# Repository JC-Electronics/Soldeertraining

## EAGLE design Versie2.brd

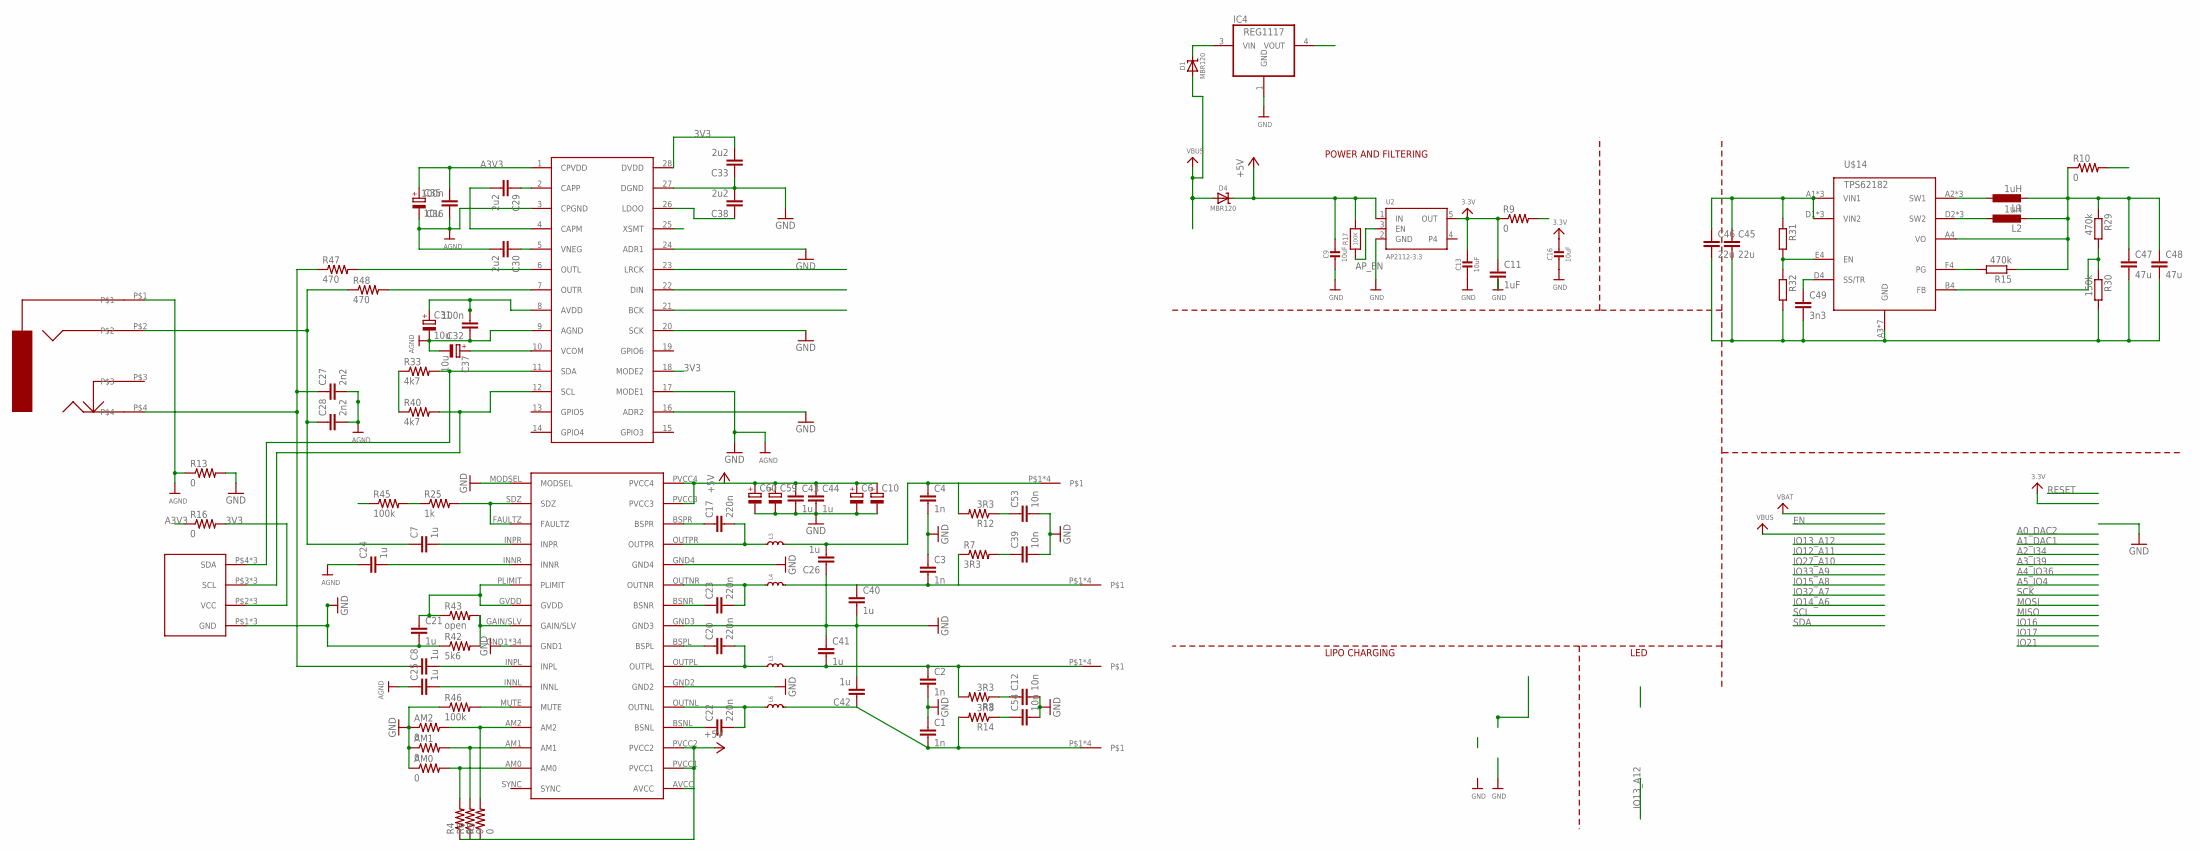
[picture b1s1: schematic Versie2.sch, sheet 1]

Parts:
AM0, AM1, AM2: 0; R0402
C1, C2, C3, C4: 1n; C0805
C6, C10, C59, C60: CPOL-EUE5-13; E5-13
C7, C8, C24, C25, C26, C40, C41, C42, C43, C44: 1u; C1206
C9, C13, C16: 10uF; 0805-NO
C11: 1uF; C1206
C12, C39, C53, C54: 10n; C0805
C17, C20, C22, C23: 220n; C0805K
C21: 1u; C0805K
C27, C28: 2n2; C0805K
C29, C30, C33, C38: 2u2; C1206K
C31, C35, C37: 10u; UD-4X5,8_NICHICON
C32, C36: 100n; C0603K
C45, C46: 22u; C0805K
C47, C48: 47u; C0805K
C49: 3n3; C0603
D1, D4: MBR120; SOD-123
IC4: REG1117; SOT223
L1, L2: 1uH; L4532P
L3, L4, L5, L6: INDUCTOR-SRN6045; SRN6045
R4, R5, R6: 0; R0402
R7, R8, R12, R14: 3R3; R0805
R9, R10, R13, R16: 0; R0805
R15, R29: 470k; R0402
R17: 100K; 0603-NO
R25: 1k; R0402
R30: 150k; R0402
R31, R32: R-EU_R0402; R0402
R33, R40: 4k7; R0805
R42: 5k6; R0402
R43: open; R0402
R45, R46: 100k; R0402
R47, R48: 470; R0805
U1: PCM5122; TSSOP-28
U2: AP2112-3.3; SOT23-5
U4: TPA3130; TSSOP32-GROUNDPAD
U$2: DISPLAY
U$9, U$16, U$22, U$23: SCREWCON
U$14: TPS62182; DSBGA24
U$26: JACKSTRAIGHTUP

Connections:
3.3V: C11.1, C13.1, C16.1, R9.1, U2.5 (OUT); also elsewhere on the board
3V3: C33.2, R9.2, R10.2, R16.2, R33.1, R40.1, U1.18 (MODE2), U1.25 (XSMT), U1.28 (DVDD), U$2.P$2 (VCC), U$2.P$10 (VCC), U$2.P$14 (VCC); also elsewhere on the board
+5V: C9.1, C45.1, C46.1, D4.C, IC4.4 (VOUT), R17.2, R31.1, U2.1 (IN), U$14.A1 (VIN1), U$14.B1 (VIN1), U$14.C1 (VIN1), U$14.D1 (VIN2), U$14.E1 (VIN2), U$14.F1 (VIN2)
A3V3: C31.+, C32.2, C35.+, C36.2, R16.1, U1.1 (CPVDD), U1.8 (AVDD)
AGND: C24.1, C25.1, C27.2, C28.2, C30.2, C31.-, C32.1, C35.-, C36.1, C37.-, R13.1, U1.3 (CPGND), U1.9 (AGND), U$26.P$1
AP_EN: R17.1, U2.3 (EN)
GND: AM0.1, AM1.1, AM2.1, C1.1, C2.2, C3.1, C4.2, C6.-, C9.2, C10.-, C11.2, C12.2, C13.2, C16.2, C21.2, C26.1, C33.1, C38.2, C39.2, C40.2, C41.1, C42.2, C43.2, C44.2, C45.2, C46.2, C47.2, C48.2, C49.2, C53.2, C54.2, C59.-, C60.-, IC4.1 (GND), R13.2, R30.2, R32.2, R42.1, R45.1, R46.1, U1.16 (ADR2), U1.17 (MODE1), U1.20 (SCK), U1.24 (ADR1), U1.27 (DGND), U2.2 (GND), U4.GND1, U4.GND2, U4.GND3, U4.GND4, U4.MODSEL, U4.P$33 (GND1), U4.P$34 (GND1), U4.P$35 (GND1), U4.P$36 (GND1), U4.P$37 (GND1), U4.P$38 (GND1), U4.P$39 (GND1), U4.P$40 (GND1), U4.P$41 (GND1), U4.P$42 (GND1), U4.P$43 (GND1), U4.P$44 (GND1), U4.P$45 (GND1), U4.P$46 (GND1), U4.P$47 (GND1), U4.P$48 (GND1), U4.P$49 (GND1), U4.P$50 (GND1), U4.P$51 (GND1), U4.P$52 (GND1), U4.P$53 (GND1), U4.P$54 (GND1), U4.P$55 (GND1), U4.P$56 (GND1), U4.P$57 (GND1), U4.P$58 (GND1), U4.P$59 (GND1), U4.P$60 (GND1), U4.P$61 (GND1), U4.P$62 (GND1), U4.P$63 (GND1), U4.P$64 (GND1), U4.POWERPAD (GND1), U$2.P$1 (GND), U$2.P$9 (GND), U$2.P$13 (GND), U$14.A3 (GND), U$14.B3 (GND), U$14.C3 (GND), U$14.C4 (GND), U$14.D3 (GND), U$14.E3 (GND), U$14.F3 (GND); also elsewhere on the board
IO18: R25.1, R45.2; also elsewhere on the board
IO25: U1.23 (LRCK); also elsewhere on the board
IO26: U1.22 (DIN); also elsewhere on the board
IO27: U1.21 (BCK); also elsewhere on the board
IO32: R40.2, U1.12 (SCL), U$2.P$3 (SCL), U$2.P$11 (SCL), U$2.P$15 (SCL); also elsewhere on the board
IO33: R33.2, U1.11 (SDA), U$2.P$4 (SDA), U$2.P$12 (SDA), U$2.P$16 (SDA); also elsewhere on the board
LEFT+: C2.1, C41.2, L5.2, R8.2, U$22.P$1, U$22.P$2, U$22.P$3, U$22.P$4
LEFT-: C1.2, C42.1, L6.2, R14.2, U$23.P$1, U$23.P$2, U$23.P$3, U$23.P$4
unnamed: C54.1, R14.1
unnamed: C53.1, R12.1
unnamed: C12.1, R8.1
unnamed: C8.1, C27.1, R47.1, U$26.P$4
unnamed: C7.1, C28.1, R48.1, U$26.P$2
unnamed: C39.1, R7.2
unnamed: C7.2, U4.INPR
unnamed: C8.2, U4.INPL
unnamed: R48.2, U1.7 (OUTR)
unnamed: R25.2, U4.FAULTZ, U4.SDZ
unnamed: C49.1, U$14.D4 (SS/TR)
unnamed: L1.1, U$14.A2 (SW1), U$14.B2 (SW1), U$14.C2 (SW1)
unnamed: L2.1, U$14.D2 (SW2), U$14.E2 (SW2), U$14.F2 (SW2)
unnamed: R15.2, U$14.F4 (PG)
unnamed: R29.2, R30.1, U$14.B4 (FB)
unnamed: R31.2, R32.1, U$14.E4 (EN)
unnamed: C24.2, U4.INNR
unnamed: C25.2, U4.INNL
unnamed: C21.1, R43.1, U4.GVDD, U4.PLIMIT
unnamed: C17.1, U4.BSPR
unnamed: C17.2, L3.1, U4.OUTPR
unnamed: C20.1, U4.BSPL
unnamed: C20.2, L5.1, U4.OUTPL
unnamed: C23.2, L4.1, U4.OUTNR
unnamed: C23.1, U4.BSNR
unnamed: C22.1, U4.BSNL
unnamed: C22.2, L6.1, U4.OUTNL
unnamed: R42.2, R43.2, U4.GAIN/SLV
unnamed: R46.2, U4.MUTE
unnamed: R47.2, U1.6 (OUTL)
unnamed: C29.2, U1.4 (CAPM)
unnamed: C29.1, U1.2 (CAPP)
unnamed: C30.1, U1.5 (VNEG)
unnamed: C37.+, U1.10 (VCOM)
unnamed: C38.1, U1.26 (LDOO)
unnamed: AM0.2, R4.2, U4.AM0
unnamed: AM1.2, R6.2, U4.AM1
unnamed: AM2.2, R5.2, U4.AM2
OUTDCDC: C47.1, C48.1, L1.2, L2.2, R10.1, R15.1, R29.1, U$14.A4 (VO); also elsewhere on the board
RIGHT+: C4.1, C26.2, L3.2, R12.2, U$9.P$1, U$9.P$2, U$9.P$3, U$9.P$4
RIGHT-: C3.2, C40.1, L4.2, R7.1, U$16.P$1, U$16.P$2, U$16.P$3, U$16.P$4
VBUS: D1.A, D4.A; also elsewhere on the board
VCC: C6.+, C10.+, C43.1, C44.1, C59.+, C60.+, D1.C, IC4.3 (VIN), R4.1, R5.1, R6.1, U4.AVCC, U4.PVCC1, U4.PVCC2, U4.PVCC3, U4.PVCC4; also elsewhere on the board

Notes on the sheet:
POWER AND FILTERING
LIPO CHARGING
LED

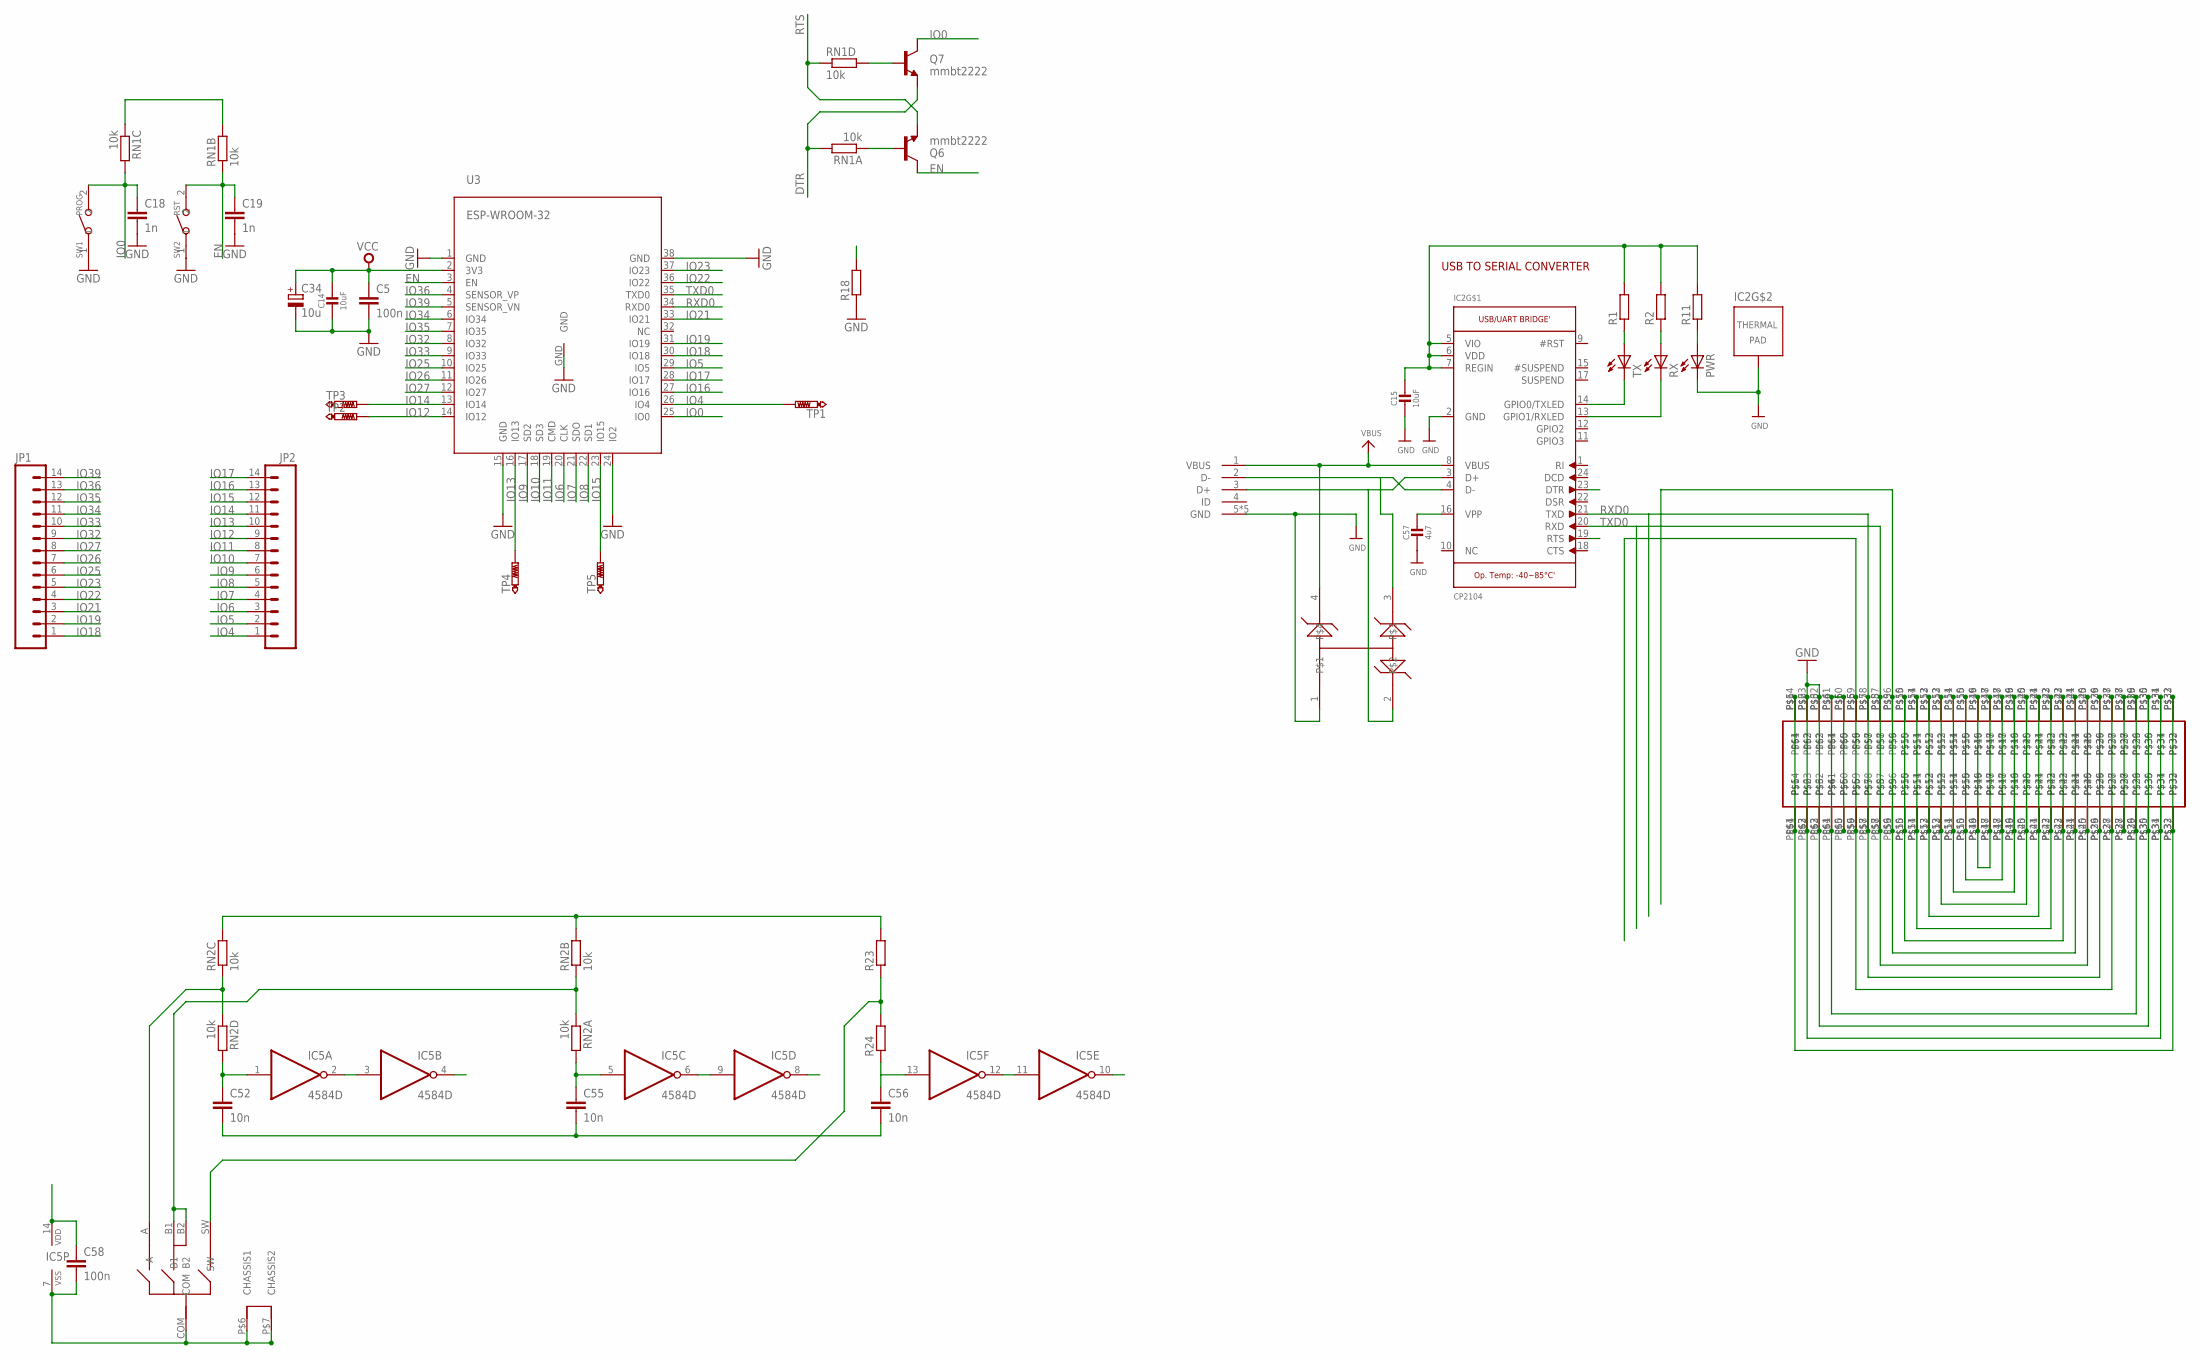
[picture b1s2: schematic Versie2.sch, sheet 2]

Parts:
C5, C58: 100n; C0603
C14, C15: 10uF; 0805-NO
C18, C19: 1n; C0805
C34: 10u; UD-4X5,8_NICHICON
C52, C55, C56: 10n; C0805
C57: 4u7; 0805-NO
D5: SP0503; SOT143
IC2: CP2104; QFN24_4MM_SMSC
IC5: 4584D; SO14
JP1, JP2: M14; 1X14
PWR: LEDCHIPLED_0603; CHIPLED_0603
Q6, Q7: mmbt2222; SOT23-3
R1, R2, R11: R-EU_R0402; R0402
R18: R-EU_R0805; R0805
R23, R24: R-EU_R0603; R0603
RN1, RN2: 10k; RN8P-4R-CRA06S
RX: LEDCHIPLED_0603; CHIPLED_0603
SW1: PROG; SW2-4.0-6.0X3.0X2.5MM
SW2: RST; SW2-4.0-6.0X3.0X2.5MM
TP1, TP2, TP3, TP4, TP5: PTR1B1,27; B1,27
TX: LEDCHIPLED_0603; CHIPLED_0603
U3: ESP-WROOM-32
U$1, U$13: 0714360864
U$41: ROTARY; ENCODER
USB: JRUSB; MICRO-B-SMT

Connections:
3.3V: U$1.P$15, U$1.P$18, U$1.P$47, U$1.P$50, U$13.P$15, U$13.P$18, U$13.P$47, U$13.P$50; also elsewhere on the board
3V3: C5.1, C14.1, C15.1, C34.+, C58.1, IC2.5 (VIO), IC2.6 (VDD), IC2.7 (REGIN), IC5.14 (VDD), R1.2, R2.2, R11.2, R23.2, RN1.3 (1), RN1.7 (2), RN2.6 (2), RN2.7 (2), U3.2 (3V3), U$1.P$16, U$1.P$17, U$1.P$48, U$1.P$49, U$13.P$16, U$13.P$17, U$13.P$48, U$13.P$49; also elsewhere on the board
DTR: IC2.23 (DTR), Q7.2 (E), RN1.8 (2)
EN: C19.1, Q6.3 (C), RN1.2 (1), SW2.2, U3.3 (EN), U$1.P$6, U$1.P$27, U$1.P$38, U$1.P$59, U$13.P$6, U$13.P$27, U$13.P$38, U$13.P$59
GND: C5.2, C14.2, C15.2, C18.2, C19.2, C34.-, C52.2, C55.2, C56.2, C57.2, C58.2, D5.1, IC2.2 (GND), IC2.THERM (TP), IC5.7 (VSS), PWR.C, R18.1, SW1.1, SW2.1, U3.1 (GND), U3.15 (GND), U3.24 (IO2), U3.38 (GND), U3.GND, U$1.P$2, U$1.P$3, U$1.P$30, U$1.P$31, U$1.P$34, U$1.P$35, U$1.P$62, U$1.P$63, U$13.P$2, U$13.P$3, U$13.P$30, U$13.P$31, U$13.P$34, U$13.P$35, U$13.P$62, U$13.P$63, U$41.COM, U$41.P$6 (CHASSIS1), U$41.P$7 (CHASSIS2), USB.5 (GND), USB.P$6 (GND), USB.P$7 (GND), USB.P$8 (GND), USB.P$9 (GND); also elsewhere on the board
GND1: R18.2
IO0: C18.1, Q7.3 (C), RN1.6 (2), SW1.2, U3.25 (IO0), U$1.P$9, U$1.P$24, U$1.P$41, U$1.P$56, U$13.P$9, U$13.P$24, U$13.P$41, U$13.P$56
IO4: JP2.1, TP1.TP, U3.26 (IO4)
IO5: IC5.10 (O), JP2.2, U3.29 (IO5)
IO6: JP2.3, U3.20 (CLK)
IO7: JP2.4, U3.21 (SDO)
IO8: JP2.5, U3.22 (SD1)
IO9: JP2.6, U3.17 (SD2)
IO10: JP2.7, U3.18 (SD3)
IO11: JP2.8, U3.19 (CMD)
IO12: JP2.9, TP2.TP, U3.14 (IO12)
IO13: JP2.10, TP4.TP, U3.16 (IO13)
IO14: JP2.11, TP3.TP, U3.13 (IO14)
IO15: JP2.12, TP5.TP, U3.23 (IO15)
IO16: IC5.8 (O), JP2.13, U3.27 (IO16)
IO17: IC5.4 (O), JP2.14, U3.28 (IO17)
IO18: JP1.1, U3.30 (IO18); also elsewhere on the board
IO19: JP1.2, U3.31 (IO19)
IO21: JP1.3, U3.33 (IO21)
IO22: JP1.4, U3.36 (IO22)
IO23: JP1.5, U3.37 (IO23)
IO25: JP1.6, U3.10 (IO25); also elsewhere on the board
IO26: JP1.7, U3.11 (IO26); also elsewhere on the board
IO27: JP1.8, U3.12 (IO27); also elsewhere on the board
IO32: JP1.9, U3.8 (IO32); also elsewhere on the board
IO33: JP1.10, U3.9 (IO33); also elsewhere on the board
IO34: JP1.11, U3.6 (IO34)
IO35: JP1.12, U3.7 (IO35)
IO36: JP1.13, U3.4 (SENSOR_VP)
IO39: JP1.14, U3.5 (SENSOR_VN)
unnamed: RN2.3 (1), RN2.4 (1), U$41.A
unnamed: D5.3, IC2.4 (D-), USB.2 (D-)
unnamed: IC5.11 (I), IC5.12 (O)
unnamed: RN2.1, RN2.2 (1), U$41.B1, U$41.B2
unnamed: C52.1, IC5.1 (I), RN2.5 (2)
unnamed: D5.2, IC2.3 (D+), USB.3 (D+)
unnamed: C55.1, IC5.5 (I), RN2.8 (2)
unnamed: R23.1, R24.2, U$41.SW
unnamed: Q7.1 (B), RN1.5 (2)
unnamed: C57.1, IC2.16 (VPP)
unnamed: Q6.1 (B), RN1.1
unnamed: PWR.A, R11.1
unnamed: IC2.14 (GPIO0/TXLED), TX.C
unnamed: IC2.13 (GPIO1/RXLED), RX.C
unnamed: R1.1, TX.A
unnamed: U$1.P$10, U$1.P$23, U$1.P$42, U$1.P$55, U$13.P$10, U$13.P$23, U$13.P$42, U$13.P$55
unnamed: U$1.P$11, U$1.P$22, U$1.P$43, U$1.P$54, U$13.P$11, U$13.P$22, U$13.P$43, U$13.P$54
unnamed: U$1.P$12, U$1.P$21, U$1.P$44, U$1.P$53, U$13.P$12, U$13.P$21, U$13.P$44, U$13.P$53
unnamed: U$1.P$13, U$1.P$20, U$1.P$45, U$1.P$52, U$13.P$13, U$13.P$20, U$13.P$45, U$13.P$52
unnamed: R2.1, RX.A
unnamed: IC5.2 (O), IC5.3 (I)
unnamed: IC5.6 (O), IC5.9 (I)
unnamed: C56.1, IC5.13 (I), R24.1
OUTDCDC: U$1.P$14, U$1.P$19, U$1.P$46, U$1.P$51, U$13.P$14, U$13.P$19, U$13.P$46, U$13.P$51; also elsewhere on the board
RTS: IC2.19 (RTS), Q6.2 (E), RN1.4 (1)
RXD0: IC2.21 (TXD), U3.34 (RXD0), U$1.P$7, U$1.P$26, U$1.P$39, U$1.P$58, U$13.P$7, U$13.P$26, U$13.P$39, U$13.P$58
TXD0: IC2.20 (RXD), U3.35 (TXD0), U$1.P$8, U$1.P$25, U$1.P$40, U$1.P$57, U$13.P$8, U$13.P$25, U$13.P$40, U$13.P$57
VBUS: D5.4, IC2.8 (VBUS), U$1.P$1, U$1.P$32, U$1.P$33, U$1.P$64, U$13.P$1, U$13.P$32, U$13.P$33, U$13.P$64, USB.1 (VBUS); also elsewhere on the board
VCC: U$1.P$4, U$1.P$5, U$1.P$28, U$1.P$29, U$1.P$36, U$1.P$37, U$1.P$60, U$1.P$61, U$13.P$4, U$13.P$5, U$13.P$28, U$13.P$29, U$13.P$36, U$13.P$37, U$13.P$60, U$13.P$61; also elsewhere on the board

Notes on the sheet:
USB TO SERIAL CONVERTER

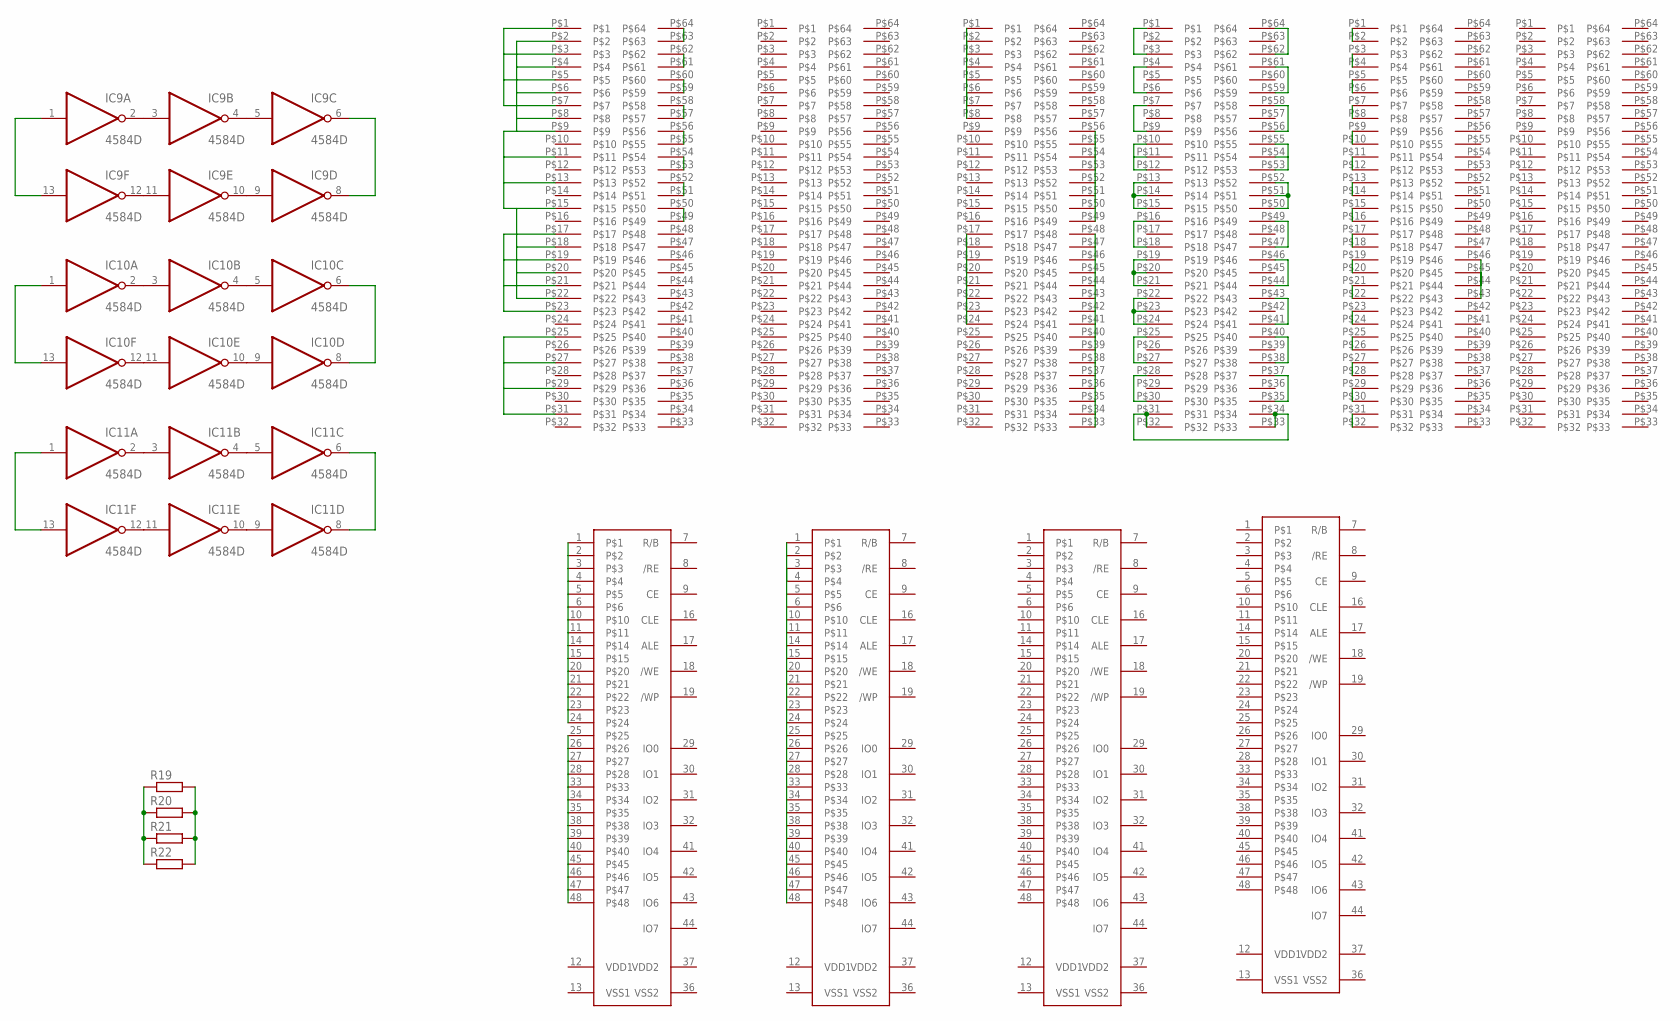
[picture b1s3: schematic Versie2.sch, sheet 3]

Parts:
IC9, IC10, IC11: 4584D; SO14
IC12, IC13, IC14, IC15: K9F5608; TSOP48
R19, R20, R21, R22: R-EU_0207/15; 0207/15
U$5, U$21, U$24, U$32, U$42, U$43: BGA64

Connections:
unnamed: IC9.2 (O), IC9.3 (I)
unnamed: IC9.4 (O), IC9.5 (I)
unnamed: IC9.9 (I), IC9.10 (O)
unnamed: IC9.6 (O), IC9.8 (O)
unnamed: IC9.1 (I), IC9.13 (I)
unnamed: IC9.11 (I), IC9.12 (O)
unnamed: IC10.2 (O), IC10.3 (I)
unnamed: IC10.4 (O), IC10.5 (I)
unnamed: IC10.9 (I), IC10.10 (O)
unnamed: IC10.6 (O), IC10.8 (O)
unnamed: IC10.1 (I), IC10.13 (I)
unnamed: IC10.11 (I), IC10.12 (O)
unnamed: IC11.2 (O), IC11.3 (I)
unnamed: IC11.4 (O), IC11.5 (I)
unnamed: IC11.9 (I), IC11.10 (O)
unnamed: IC11.6 (O), IC11.8 (O)
unnamed: IC11.1 (I), IC11.13 (I)
unnamed: IC11.11 (I), IC11.12 (O)
unnamed: R19.1, R20.1, R21.1, R22.1
unnamed: R19.2, R20.2, R21.2, R22.2
unnamed: U$5.P$17, U$5.P$19, U$5.P$21, U$5.P$23
unnamed: IC13.1, IC13.2, IC13.3, IC13.4, IC13.5, IC13.6, IC13.10, IC13.11, IC13.14, IC13.15, IC13.20, IC13.21, IC13.22, IC13.23, IC13.24
unnamed: U$42.P$27, U$42.P$28
unnamed: U$42.P$29, U$42.P$30
unnamed: U$42.P$25, U$42.P$26
unnamed: U$42.P$23, U$42.P$24
unnamed: U$42.P$21, U$42.P$22
unnamed: U$42.P$19, U$42.P$20
unnamed: U$42.P$17, U$42.P$18
unnamed: U$42.P$15, U$42.P$16
unnamed: U$42.P$13, U$42.P$14
unnamed: U$42.P$11, U$42.P$12
unnamed: U$42.P$9, U$42.P$10
unnamed: U$42.P$7, U$42.P$8
unnamed: U$42.P$5, U$42.P$6
unnamed: U$42.P$3, U$42.P$4
unnamed: U$42.P$1, U$42.P$2
unnamed: U$42.P$31, U$42.P$32
unnamed: U$32.P$62, U$32.P$64
unnamed: U$32.P$59, U$32.P$61
unnamed: U$32.P$56, U$32.P$58
unnamed: U$32.P$53, U$32.P$54, U$32.P$55
unnamed: U$32.P$50, U$32.P$51, U$32.P$52
unnamed: U$32.P$47, U$32.P$49
unnamed: U$32.P$44, U$32.P$46
unnamed: U$32.P$41, U$32.P$43
unnamed: U$32.P$38, U$32.P$40
unnamed: U$32.P$35, U$32.P$37
unnamed: U$5.P$1, U$5.P$3, U$5.P$5, U$5.P$7
unnamed: U$5.P$63, U$5.P$64
unnamed: U$5.P$25, U$5.P$27, U$5.P$29, U$5.P$31
unnamed: U$5.P$2, U$5.P$4, U$5.P$6, U$5.P$8, U$5.P$9, U$5.P$11, U$5.P$13, U$5.P$15, U$5.P$18, U$5.P$20, U$5.P$22
unnamed: U$5.P$61, U$5.P$62
unnamed: U$5.P$59, U$5.P$60
unnamed: U$5.P$57, U$5.P$58
unnamed: U$5.P$55, U$5.P$56
unnamed: U$5.P$53, U$5.P$54
unnamed: U$5.P$51, U$5.P$52
unnamed: U$5.P$49, U$5.P$50
unnamed: U$42.P$43, U$42.P$44, U$42.P$45, U$42.P$46
unnamed: U$32.P$1, U$32.P$3
unnamed: U$32.P$4, U$32.P$6
unnamed: U$32.P$7, U$32.P$9
unnamed: U$32.P$10, U$32.P$11, U$32.P$12
unnamed: U$32.P$13, U$32.P$14, U$32.P$15
unnamed: U$32.P$16, U$32.P$18
unnamed: U$32.P$19, U$32.P$20, U$32.P$21
unnamed: U$32.P$22, U$32.P$23, U$32.P$24
unnamed: U$32.P$25, U$32.P$27
unnamed: U$32.P$28, U$32.P$30
unnamed: U$32.P$31, U$32.P$32, U$32.P$33, U$32.P$34
unnamed: U$24.P$1, U$24.P$2, U$24.P$3, U$24.P$4, U$24.P$5, U$24.P$6, U$24.P$7, U$24.P$8
unnamed: U$24.P$17, U$24.P$18, U$24.P$19, U$24.P$20, U$24.P$21, U$24.P$22, U$24.P$23, U$24.P$24
unnamed: U$24.P$49, U$24.P$50, U$24.P$51, U$24.P$52, U$24.P$53, U$24.P$54, U$24.P$55, U$24.P$56
unnamed: U$24.P$33, U$24.P$34, U$24.P$35, U$24.P$36, U$24.P$37, U$24.P$38, U$24.P$39, U$24.P$40, U$24.P$41, U$24.P$42, U$24.P$43, U$24.P$44, U$24.P$45, U$24.P$46, U$24.P$47, U$24.P$48
unnamed: IC13.25, IC13.26, IC13.27, IC13.28, IC13.33, IC13.34, IC13.35, IC13.38, IC13.39, IC13.40, IC13.45, IC13.46, IC13.47, IC13.48
unnamed: IC14.1, IC14.2, IC14.3, IC14.4, IC14.5, IC14.6, IC14.10, IC14.11, IC14.14, IC14.15, IC14.20, IC14.21, IC14.22, IC14.23, IC14.24, IC14.25, IC14.26, IC14.27, IC14.28, IC14.33, IC14.34, IC14.35, IC14.38, IC14.39, IC14.40, IC14.45, IC14.46, IC14.47, IC14.48
VDD: IC9.14 (VDD), IC10.14 (VDD), IC11.14 (VDD)
VDD1: IC12.12 (VDD1), IC13.12 (VDD1), IC14.12 (VDD1), IC15.12 (VDD1)
VDD2: IC12.37 (VDD2), IC13.37 (VDD2), IC14.37 (VDD2), IC15.37 (VDD2)
VSS: IC9.7 (VSS), IC10.7 (VSS), IC11.7 (VSS)
VSS1: IC12.13 (VSS1), IC13.13 (VSS1), IC14.13 (VSS1), IC15.13 (VSS1)
VSS2: IC12.36 (VSS2), IC13.36 (VSS2), IC14.36 (VSS2), IC15.36 (VSS2)

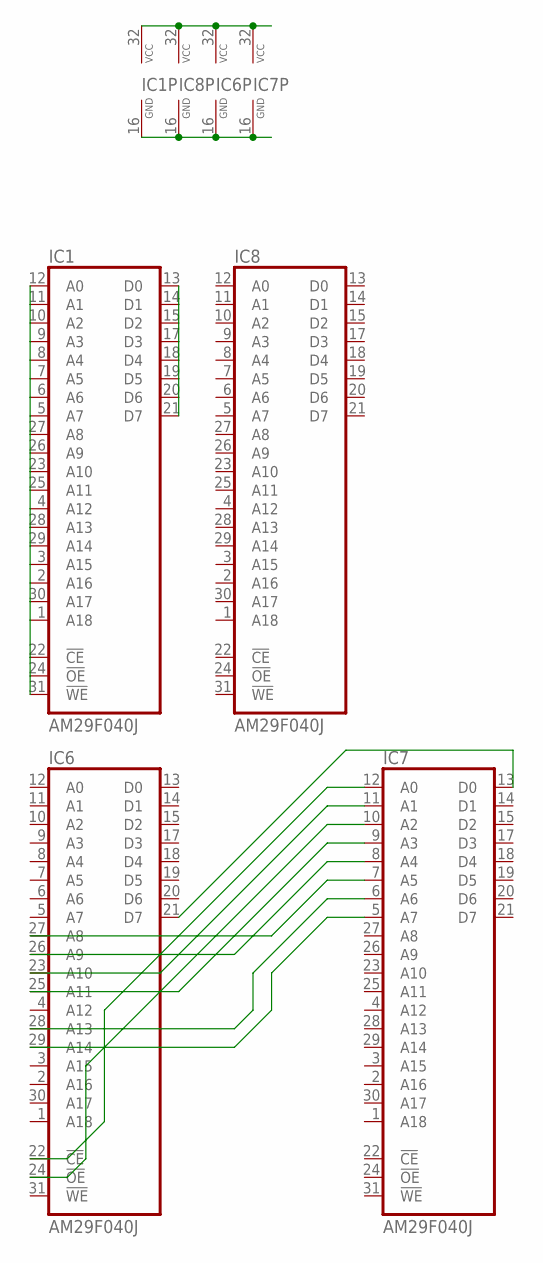
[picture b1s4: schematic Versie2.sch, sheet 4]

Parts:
IC1, IC6, IC7, IC8: AM29F040J; PLCC32R

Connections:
unnamed: IC1.16 (GND), IC6.16 (GND), IC7.16 (GND), IC8.16 (GND)
unnamed: IC1.32 (VCC), IC6.32 (VCC), IC7.32 (VCC), IC8.32 (VCC)
unnamed: IC6.29 (A14), IC7.5 (A7)
unnamed: IC6.28 (A13), IC7.6 (A6)
unnamed: IC6.27 (A8), IC7.7 (A5)
unnamed: IC6.26 (A9), IC7.8 (A4)
unnamed: IC6.25 (A11), IC7.9 (A3)
unnamed: IC6.24 (!OE), IC7.10 (A2)
unnamed: IC6.23 (A10), IC7.11 (A1)
unnamed: IC6.22 (!CE), IC7.12 (A0)
unnamed: IC6.21 (D7), IC7.13 (D0)
unnamed: IC1.1 (A18), IC1.2 (A16), IC1.3 (A15), IC1.4 (A12), IC1.5 (A7), IC1.6 (A6), IC1.7 (A5), IC1.8 (A4), IC1.9 (A3), IC1.10 (A2), IC1.11 (A1), IC1.12 (A0), IC1.22 (!CE), IC1.23 (A10), IC1.24 (!OE), IC1.25 (A11), IC1.26 (A9), IC1.27 (A8), IC1.28 (A13), IC1.29 (A14), IC1.30 (A17), IC1.31 (!WE)
unnamed: IC1.13 (D0), IC1.14 (D1), IC1.15 (D2), IC1.17 (D3), IC1.18 (D4), IC1.19 (D5), IC1.20 (D6), IC1.21 (D7)

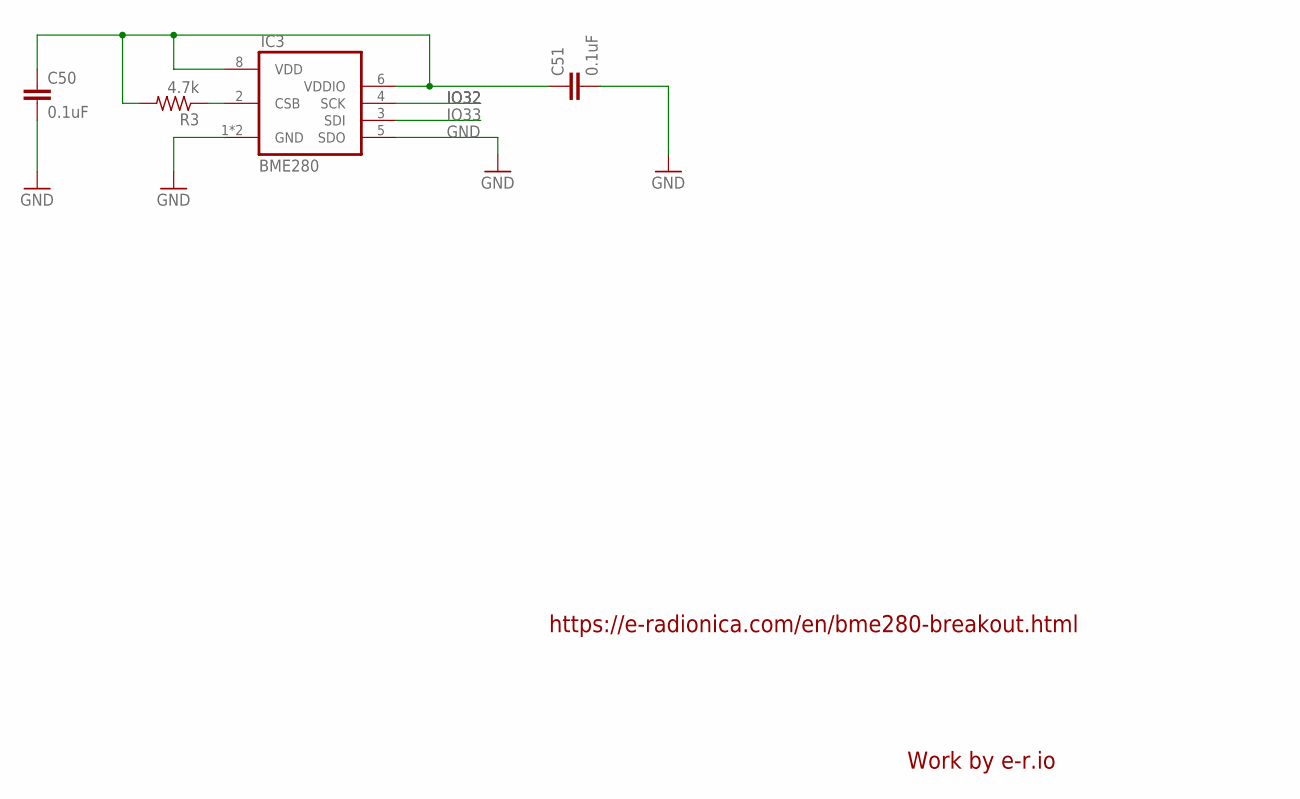
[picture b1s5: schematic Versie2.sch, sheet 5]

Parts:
C50, C51: 0.1uF; 0603
IC3: BME280
R3: 4.7k; R0805

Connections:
3V3: C50.1, C51.1, IC3.6 (VDDIO), IC3.8 (VDD), R3.2; also elsewhere on the board
GND: C50.2, C51.2, IC3.1 (GND), IC3.5 (SDO), IC3.7 (GND); also elsewhere on the board
IO32: IC3.4 (SCK); also elsewhere on the board
IO33: IC3.3 (SDI); also elsewhere on the board
unnamed: IC3.2 (CSB), R3.1

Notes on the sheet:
https://e-radionica.com/en/bme280-breakout.html
Work by e-r.io

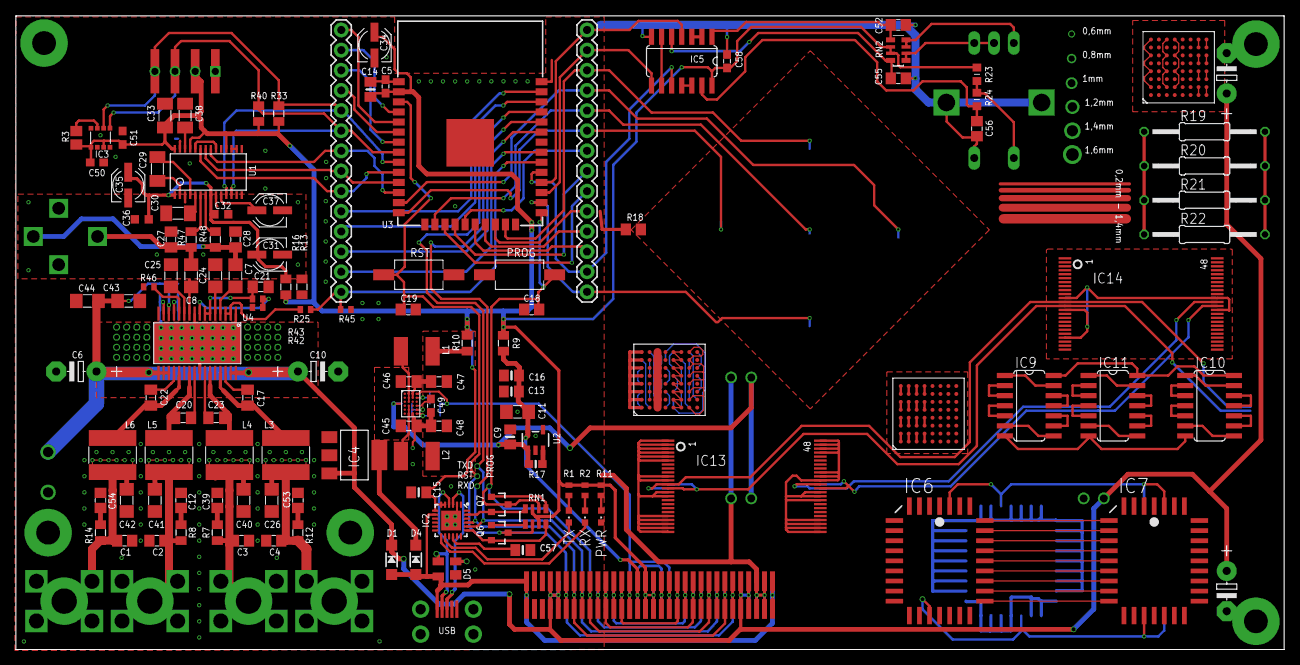
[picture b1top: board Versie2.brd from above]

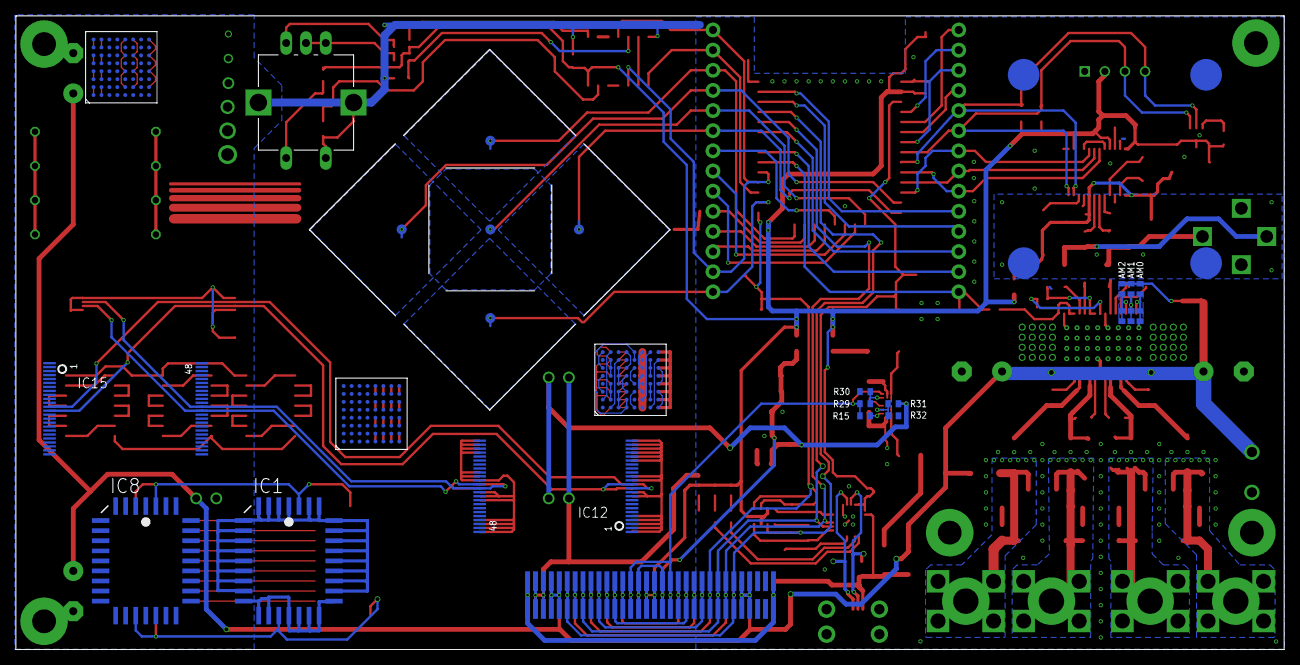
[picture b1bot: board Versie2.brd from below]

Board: 2 copper layers, 159.9 x 79.9 mm, 161 parts (26 on the bottom side), 206 nets.

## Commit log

2018-02-03 Jos - 03FEB2018
2018-02-03 Jos - 03FAB2018
2018-02-07 Bleutooth branch
2018-02-08 Jos - 08FEB2018

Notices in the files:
parts and their libraries:
microbuilder: This work is placed in the public domain, and may be freely used for commercial and non-commercial work with the following conditions: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
SparkFun-Connectors: Licensing: Creative Commons ShareAlike 4.0 International - https://creativecommons.org/licenses/by-sa/4.0
